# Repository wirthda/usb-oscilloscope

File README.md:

# Introduction
This repository serves as documentation and overview of the project **USB-oscilloscope**,
which was carried out in the summer semester 2025 at the efi faculty of the University of Applied Sciences Nuremberg (Georg-Simon-Ohm).
# Overview
### Project structure:

<ins>legend:</ins>\
HW - hardware\
FW - firmware\
SW - software

### USB oscilloscope prototype:

### Documentation:
PDF [GER]: [Dokumentation_Projekt_USB_Oszi.pdf](docs/documentation/LATEX_german/Dokumentation_Projekt_USB_Oszi.pdf)

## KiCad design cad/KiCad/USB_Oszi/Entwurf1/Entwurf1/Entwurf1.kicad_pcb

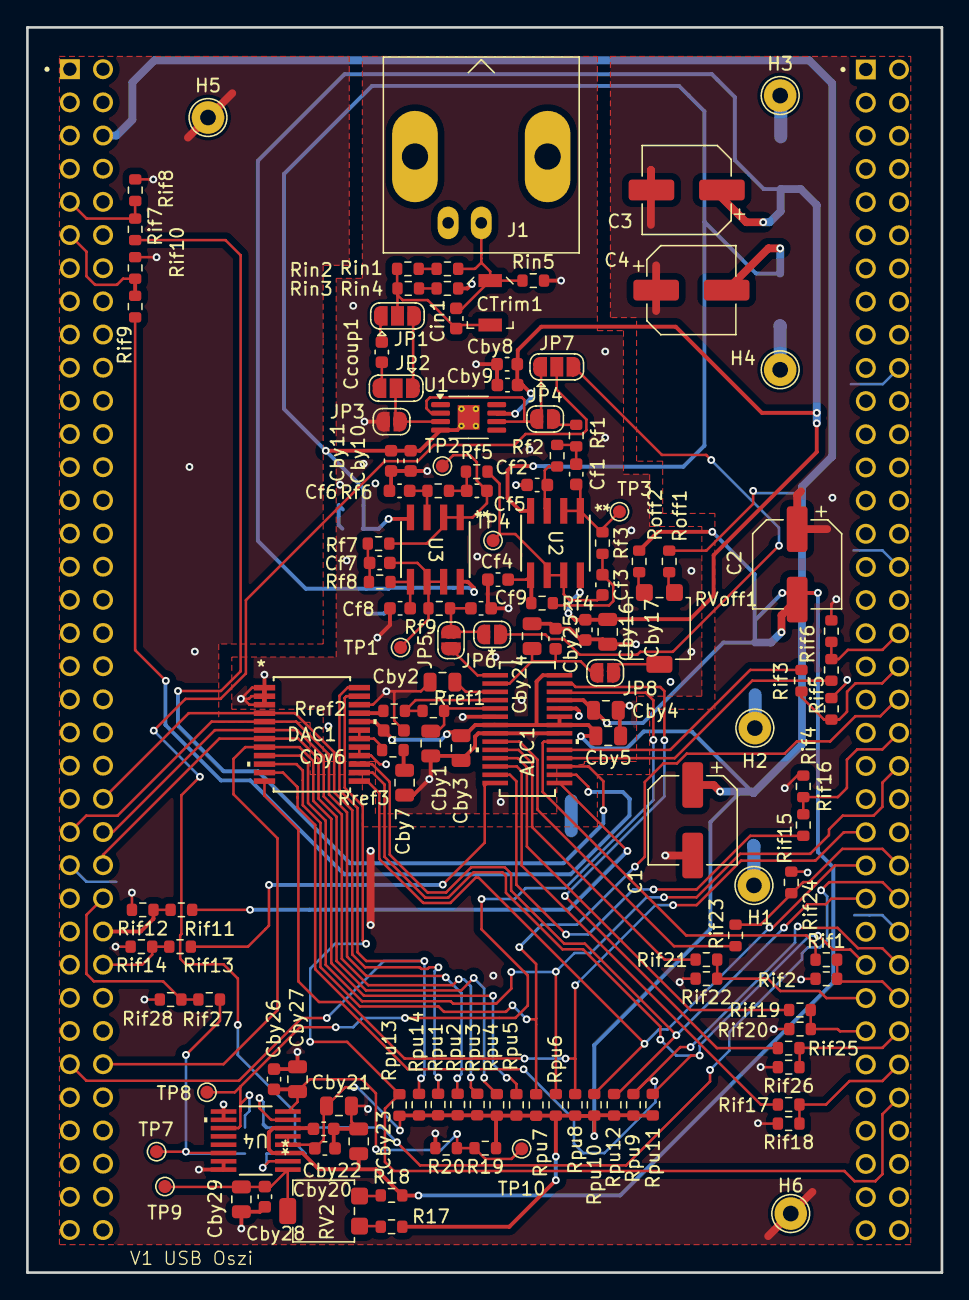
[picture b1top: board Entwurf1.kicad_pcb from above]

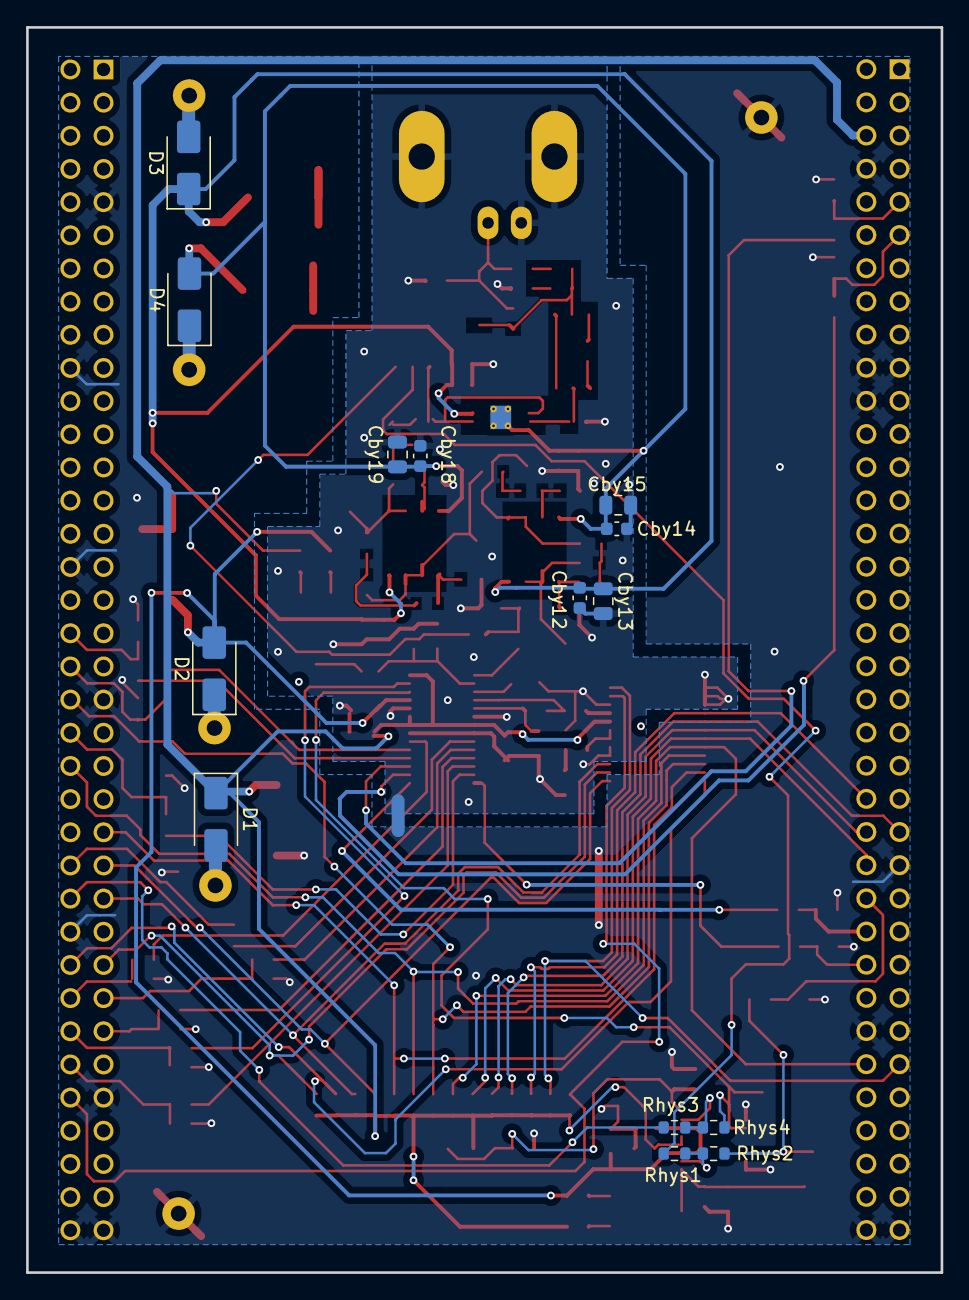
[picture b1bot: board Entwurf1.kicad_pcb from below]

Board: 2 copper layers, 70.0 x 95.4 mm, 150 parts (14 on the bottom side), 95 nets.

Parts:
A1: NUCLEO-F767ZI; ST_NUCLEO-F767ZI
ADC1: LTC1420CGN-PBF; FOOTPRINT_ADC_USB_OSZI
C1, C2, C3, C4: C_Polarized; CP_Elec_6.3x7.7
CTrim1: Cin2; C_Trimmer_Voltronics_JR
Cby1, Cby2, Cby3, Cby4, Cby5, Cby24: 1u; C_0805_2012Metric
Cby6, Cby8, Cby10, Cby12, Cby14, Cby16, Cby18, Cby20, Cby22, Cby26, Cby28: 0.1u; C_0603_1608Metric
Cby7, Cby21, Cby23, Cby27, Cby29: 4.7u; C_0805_2012Metric
Cby9, Cby11: 100p; C_0603_1608Metric
Cby13, Cby15, Cby17, Cby19: 10u; C_0805_2012Metric
Cby25: 100n; C_0603_1608Metric
Ccoup1: C; C_0603_1608Metric
Cf1, Cf2, Cf3, Cf4, Cf5, Cf6, Cf7, Cf8, Cf9: C; C_0603_1608Metric
Cin1: C; C_0603_1608Metric
D1, D2, D3, D4: D_Schottky; D_SMA
DAC1: LTC1450CG-PBF; SSOP-24_G_LIT
H1: +5V; TestPoint_THTPad_D2.5mm_Drill1.2mm
H2: -5V; TestPoint_THTPad_D2.5mm_Drill1.2mm
H3: V+; TestPoint_THTPad_D2.5mm_Drill1.2mm
H4: V-; TestPoint_THTPad_D2.5mm_Drill1.2mm
H5, H6: GND; TestPoint_THTPad_D2.5mm_Drill1.2mm
J1: BNC_CH1; BNC_Amphenol_B6252HB-NPP3G-50_Horizontal
JP1, JP2, JP7: coupling; SolderJumper-3_P1.3mm_Open_RoundedPad1.0x1.5mm
JP3, JP4, JP5, JP6, JP8: coupling; SolderJumper-2_P1.3mm_Open_RoundedPad1.0x1.5mm
R17, R18: 820; R_0603_1608Metric
R19: 68k; R_0603_1608Metric
R20: 33k; R_0603_1608Metric
RV2: 10k; Potentiometer_Bourns_3314G_Vertical
RVoff1: 5k; Potentiometer_Bourns_3314G_Vertical
Rf1, Rf2, Rf3, Rf4, Rf5, Rf6, Rf7, Rf8, Rf9: R; R_0603_1608Metric
Rhys1, Rhys3: 100; R_0603_1608Metric
Rhys2, Rhys4: 50k; R_0603_1608Metric
Rif1, Rif2, Rif3, Rif4, Rif5, Rif6, Rif7, Rif8, Rif9, Rif10, Rif11, Rif12, Rif13, Rif14, Rif15, Rif16, Rif17, Rif18, Rif19, Rif20, Rif21, Rif22, Rif23, Rif24, Rif25, Rif26, Rif27, Rif28: R; R_0603_1608Metric
Rin1: 30k; R_0603_1608Metric
Rin2: 560k; R_0603_1608Metric
Rin3: 20k; R_0603_1608Metric
Rin4: 390k; R_0603_1608Metric
Rin5: 50; R_0603_1608Metric
Roff1, Roff2: 2.7k; R_0603_1608Metric
Rpu1, Rpu2, Rpu3, Rpu4, Rpu5, Rpu6, Rpu7, Rpu8, Rpu9, Rpu10, Rpu11, Rpu12, Rpu13, Rpu14: 10k; R_0603_1608Metric
Rref1, Rref2: 5k; R_0603_1608Metric
Rref3: 10; R_0603_1608Metric
TP1: OPV4_OUT; TestPoint_Pad_D1.0mm
TP2: OPV3_OUT; TestPoint_Pad_D1.0mm
TP3: OPV1_OUT; TestPoint_Pad_D1.0mm
TP4: OPV2_OUT; TestPoint_Pad_D1.0mm
TP7: TRIGGER; TestPoint_Pad_D1.0mm
TP8: 5V_CLK; TestPoint_Pad_D1.0mm
TP9: TRIGGER_REF; TestPoint_Pad_D1.0mm
TP10: CLK_REF; TestPoint_Pad_D1.0mm
U1: THS4631DGN; MSOP-8-1EP_3x3mm_P0.65mm_EP1.68x1.88mm_ThermalVias
U2, U3: AD8022ARZ-REEL7; R_8_ADI
U4: LT1714CGN-PBF; SSOP-16_GN_LIT

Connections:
+5V: A1.CN11_6 (E5V), ADC1.7 (VDD), ADC1.22 (OVDD), ADC1.23 (VDD), ADC1.28 (GAIN), C1.1, Cby3.1, Cby5.2, Cby6.1, Cby20.1, Cby21.1, D1.1 (K), DAC1.20 (VCC), R17.1, R19.1, Roff1.1, Rpu1.1, Rpu2.1, Rpu3.1, Rpu4.1, Rpu5.1, Rpu6.1, Rpu7.1, Rpu8.1, Rpu9.1, Rpu10.1, Rpu11.1, Rpu12.1, Rpu13.1, Rpu14.1, U4.4 (V+), U4.5 (V+)
-5V: ADC1.25 (VSS), C2.2, Cby4.1, Cby22.1, Cby23.1, D2.2 (A), R18.2, Roff2.2, U4.3 (V-), U4.6 (V-)
/ADC1/ADC1_CLK: ADC1.26 (CLK), Rhys4.2, TP8.1, U4.11 (QB)
/ADC1/ADC1_D0: ADC1.20 (D0), Rif1.1
/ADC1/ADC1_D1: ADC1.19 (D1), Rif3.1
/ADC1/ADC1_D2: ADC1.18 (D2), Rif5.1
/ADC1/ADC1_D3: ADC1.17 (D3), Rif7.1
/ADC1/ADC1_D4: ADC1.16 (D4), Rif9.1
/ADC1/ADC1_D5: ADC1.15 (D5), Rif11.1
/ADC1/ADC1_D6: ADC1.14 (D6), Rif13.1
/ADC1/ADC1_D7: ADC1.13 (D7), Rif15.1
/ADC1/ADC1_D8: ADC1.12 (D8), Rif17.1
/ADC1/ADC1_D9: ADC1.11 (D9), Rif19.1
/ADC1/ADC1_D10: ADC1.10 (D10), Rif21.1
/ADC1/ADC1_D11: ADC1.9 (D11(MSB)), Rif23.1
/ADC1/ADC1_INPUT: ADC1.1 (+AIN), JP5.2 (B)
/ADC1/ADC1_OF_BIT: ADC1.27 (OF), Rif25.1
/ADC1/DAC1_CLEAR_LOW_ACTIVE: A1.CN12_64 (PE0), DAC1.23 (*CLR), Rpu13.2
/ADC1/DAC1_LOAD_LOW_ACTIVE: A1.CN11_61 (PE1), DAC1.24 (*LDAC), Rpu14.2
/Analog Frontend CH1/ANALOG_INPUT: CTrim1.1, Cin1.1, J1.1 (In), Rin1.1, Rin5.1
/Analog Frontend CH1/TRIGGER_SIGNAL: JP7.2 (C), Rhys1.1
/Connector uC/PE2: A1.CN11_46 (PE2), DAC1.4 ((LSB)D0), Rpu1.2
/Connector uC/PE3: A1.CN11_47 (PE3), DAC1.5 (D1), Rpu2.2
/Connector uC/PE4: A1.CN11_48 (PE4), DAC1.6 (D2), Rpu3.2
/Connector uC/PE5: A1.CN11_50 (PE5), DAC1.7 (D3), Rpu4.2
/Connector uC/PE6: A1.CN11_62 (PE6), DAC1.8 (D4), Rpu5.2
/Connector uC/PE7: A1.CN12_44 (PE7), DAC1.9 (D5), Rpu6.2
/Connector uC/PE8: A1.CN12_40 (PE8), DAC1.10 (D6), Rpu7.2
/Connector uC/PE9: A1.CN12_52 (PE9), Rhys3.1
/Connector uC/PE10: A1.CN12_47 (PE10), DAC1.11 (D7), Rpu8.2
/Connector uC/PE11: A1.CN12_56 (PE11), DAC1.12 (D8), Rpu9.2
/Connector uC/PE12: A1.CN12_49 (PE12), DAC1.13 (D9), Rpu10.2
/Connector uC/PE13: A1.CN12_55 (PE13), DAC1.14 (D10), Rpu11.2
/Connector uC/PE14: A1.CN12_51 (PE14), DAC1.15 (D11(MSB)), Rpu12.2
/Connector uC/PF2: A1.CN11_52 (PF2), Rif27.2, Rif28.1
/Connector uC/PF3: A1.CN12_58 (PF3), Rif1.2, Rif2.1
/Connector uC/PF4: A1.CN12_38 (PF4), Rif3.2, Rif4.1
/Connector uC/PF5: A1.CN12_36 (PF5), Rif5.2, Rif6.1
/Connector uC/PF6: A1.CN11_9 (PF6), Rif7.2, Rif8.1
/Connector uC/PF7: A1.CN11_11 (PF7), Rif9.2, Rif10.1
/Connector uC/PF8: A1.CN11_54 (PF8), Rif11.2, Rif12.1
/Connector uC/PF9: A1.CN11_56 (PF9), Rif13.2, Rif14.1
/Connector uC/PF10: A1.CN12_42 (PF10), Rif15.2, Rif16.1
/Connector uC/PF11: A1.CN12_62 (PF11), Rif17.2, Rif18.1
/Connector uC/PF12: A1.CN12_59 (PF12), Rif19.2, Rif20.1
/Connector uC/PF13: A1.CN12_57 (PF13), Rif21.2, Rif22.1
/Connector uC/PF14: A1.CN12_50 (PF14), Rif23.2, Rif24.1
/Connector uC/PF15: A1.CN12_60 (PF15), Rif25.2, Rif26.1
/Interface uC/5V_TRIGGERED_SIG_IN: Rhys2.1, Rif27.1, TP7.1, U4.14 (QA)
GNDA: A1.CN11_8 (GND_CN11), A1.CN11_19 (GND_CN11__1), A1.CN11_20 (GND_CN11__2), A1.CN11_22 (GND_CN11__3), A1.CN11_49 (GND_CN11__4), A1.CN11_60 (GND_CN11__5), A1.CN11_71 (GND_CN11__6), A1.CN11_72 (GND_CN11__7), A1.CN12_9 (GND_CN12), A1.CN12_20 (GND_CN12__1), A1.CN12_32 (AGND_CN12), A1.CN12_39 (GND_CN12__2), A1.CN12_54 (GND_CN12__3), A1.CN12_63 (GND_CN12__4), A1.CN12_71 (GND_CN12__5), A1.CN12_72 (GND_CN12__6), ADC1.6 (GND), ADC1.8 (GND), ADC1.21 (OGND), ADC1.24 (GND), C1.2, C2.1, C3.2, C4.1, Cby1.2, Cby2.2, Cby3.2, Cby4.2, Cby5.1, Cby6.2, Cby7.2, Cby8.2, Cby9.2, Cby10.2, Cby11.2, Cby12.2, Cby13.2, Cby14.2, Cby15.2, Cby16.2, Cby17.2, Cby18.2, Cby19.2, Cby20.2, Cby21.2, Cby22.2, Cby23.2, Cby24.2, Cby25.2, Cby26.2, Cby27.2, Cby28.2, Cby29.2, Cf2.2, Cf4.2, Cf6.2, Cf8.2, Cf9.2, DAC1.1 (*WR), DAC1.2 (*CSLSB), DAC1.3 (*CSMSB), DAC1.16 (GND), DAC1.17 (REFLO), DAC1.22 (X1/X2), H5.1, H6.1, J1.2 (Ext), JP3.2 (B), R20.2, Rif2.2, Rif4.2, Rif6.2, Rif8.2, Rif10.2, Rif12.2, Rif14.2, Rif16.2, Rif18.2, Rif20.2, Rif22.2, Rif24.2, Rif26.2, Rif28.2, Rin4.2, Rin5.2, U4.9 (LATCHENABLEB), U4.10 (GND), U4.15 (GND), U4.16 (LATCHENABLEA)
unnamed: ADC1.2 (-AIN), Cby24.1, Cby25.1, JP8.2 (B)
unnamed: ADC1.4 (SENSE), Rref1.2, Rref2.1
unnamed: ADC1.3 (VCM), Cby2.1
unnamed: ADC1.5 (VREF), Cby1.1, Rref1.1
unnamed: Cby7.1, Rref3.2
unnamed: Cf1.2, Rf1.2, Rf2.1
unnamed: Cf3.1, Rf3.2, Rf4.1
unnamed: Cf5.2, Rf5.2, Rf6.1
unnamed: Cf7.1, Rf7.2, Rf8.1
unnamed: D1.2 (A), H1.1
unnamed: D2.1 (K), H2.1
unnamed: D3.2 (A), H3.1
unnamed: D4.1 (K), H4.1
unnamed: DAC1.18 (REFHI), DAC1.19 (REFOUT), Rref3.1
unnamed: DAC1.21 (VOUT), Rref2.2
unnamed: Ccoup1.1, JP1.1 (A)
unnamed: JP1.3 (B), JP2.1 (A)
unnamed: CTrim1.2, Cin1.2, JP1.2 (C), Rin2.2, Rin3.1
unnamed: Ccoup1.2, JP2.3 (B)
unnamed: JP2.2 (C), JP3.1 (A), U1.3 (+)
unnamed: JP4.1 (A), JP7.1 (A), U1.2 (-), U1.6
unnamed: JP4.2 (B), Rf1.1
unnamed: Cf9.1, JP5.1 (A), JP6.1 (A), Rf9.2
unnamed: JP6.2 (B), JP7.3 (B)
unnamed: JP8.1 (A), RVoff1.2
unnamed: R17.2, RV2.1
unnamed: R18.1, RV2.3
unnamed: RVoff1.1, Roff1.2
unnamed: RVoff1.3, Roff2.1
unnamed: Rin1.2, Rin2.1
unnamed: Rin3.2, Rin4.1
unnamed: Cf2.1, Rf2.2, U2.3 (+IN1)
unnamed: Cf4.1, Rf4.2, U2.5 (+IN2)
unnamed: Cf1.1, Rf3.1, TP3.1, U2.1 (OUT1), U2.2 (-IN1)
unnamed: Cf3.2, Rf5.1, TP4.1, U2.6 (-IN2), U2.7 (OUT2)
unnamed: Cf6.1, Rf6.2, U3.3 (+IN1)
unnamed: Cf8.1, Rf8.2, U3.5 (+IN2)
unnamed: Cf5.1, Rf7.1, TP2.1, U3.1 (OUT1), U3.2 (-IN1)
unnamed: Cf7.2, Rf9.1, TP1.1, U3.6 (-IN2), U3.7 (OUT2)
unnamed: Rhys1.2, Rhys2.2, U4.2 (+INA)
unnamed: Rhys3.2, Rhys4.1, U4.7 (+INB)
unnamed: Cby28.1, Cby29.1, RV2.2, TP9.1, U4.1 (-INA)
unnamed: Cby26.1, Cby27.1, R19.2, R20.1, TP10.1, U4.8 (-INB)
V+: C3.1, Cby8.1, Cby9.1, Cby12.1, Cby13.1, Cby16.1, Cby17.1, D3.1 (K), U1.7 (V+), U2.8 (+VS), U3.8 (+VS)
V-: C4.2, Cby10.1, Cby11.1, Cby14.1, Cby15.1, Cby18.1, Cby19.1, D4.2 (A), U1.4 (V-), U1.9 (PAD), U2.4 (-VS), U3.4 (-VS)

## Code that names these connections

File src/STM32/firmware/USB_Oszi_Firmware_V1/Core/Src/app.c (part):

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 * configures the external DAC (LTC1450) to set the ADC reference voltage in mV
 * according to the variable newReferenceVoltage (value sent over from PC)
 *
 * µC[PE14:PE10, PE8:PE2] --> DAC[D11:D0]
 * PE0: /CLEAR
 * PE1: /LOAD
 * 														*/
void configureReferenceVoltage()
{
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
	uint16_t DAC_ODR_val = 0, temp;

	// set bits DAC[D0:D6] ( µC[PE2:PE8] )
	temp = DAC_val & MASK_D0_D6;				// extract DAC[D0:D6]
	DAC_ODR_val |= (temp << 2);		// prepare assignment to µC[PE2:PE8]
	// set bits DAC[D7:D11] ( µC[PE10:PE14] )
	temp = (DAC_val & MASK_D7_D11) >> 7;			// extract DAC[D7:D11] and flush right
	DAC_ODR_val |= (temp << 10);		// prepare assignment to µC[PE10:PE14]

	// clear µC[PE2:PE8, PE10:PE14]
	GPIOE->ODR &= ~(GPIO_ODR_OD2|GPIO_ODR_OD3|GPIO_ODR_OD4|GPIO_ODR_OD5|GPIO_ODR_OD6|GPIO_ODR_OD7|GPIO_ODR_OD8|
				    GPIO_ODR_OD10|GPIO_ODR_OD11|GPIO_ODR_OD12|GPIO_ODR_OD13|GPIO_ODR_OD14);
	GPIOE->ODR |= DAC_ODR_val;					// assign DAC[D0:D11]
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	/* --- ADC-GPIOs --- */

	/* GPIOs for ADC parallel interface
	 * ADC[D11:D0] --> µC[PF14:PF3]	*/
	/* enable clock for GPIOF */
	RCC->AHB1ENR |= RCC_AHB1ENR_GPIOFEN;
	// PF3...14->input (MODE: 0b00)
	GPIOF->MODER &= ~(GPIO_MODER_MODER3_Msk|GPIO_MODER_MODER4_Msk|GPIO_MODER_MODER5_Msk|GPIO_MODER_MODER6_Msk|
					  GPIO_MODER_MODER7_Msk|GPIO_MODER_MODER8_Msk|GPIO_MODER_MODER9_Msk|GPIO_MODER_MODER10_Msk|
					  GPIO_MODER_MODER11_Msk|GPIO_MODER_MODER12_Msk|GPIO_MODER_MODER13_Msk|GPIO_MODER_MODER14_Msk);
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	GPIOF->PUPDR |= GPIO_PUPDR_PUPDR15_1|GPIO_PUPDR_PUPDR2_1|GPIO_PUPDR_PUPDR1_1|GPIO_PUPDR_PUPDR0_1;

	/* GPIO for ADC Overflow Flag
	 * ADC[OF_BIT] --> µC[PF15]	 	*/
	/* enable clock for GPIOF */
	RCC->AHB1ENR |= RCC_AHB1ENR_GPIOFEN;
	// PF15->input (MODE: 0b00)
	GPIOF->MODER &= ~(GPIO_MODER_MODER15_Msk);

	/* GPIO for Trigger
	 * TRIGGERED_SIG_OUT --> µC[PF2]*/
	/* enable clock for GPIOF */
	RCC->AHB1ENR |= RCC_AHB1ENR_GPIOFEN;
	// PF2->input (MODE: 0b00)
	GPIOF->MODER &= ~(GPIO_MODER_MODER2_Msk);


	/* GPIO for TIMer output compare event
	 * PE9: TIM1_CH1 (AF1)
	 * clock for ADC, triggers DMA2 channel 6 stream 5 transfers*/
	/* enable clock for GPIOE */
	RCC->AHB1ENR |= RCC_AHB1ENR_GPIOEEN;
	// PE9->alternate function (MODE: 0b10)
	GPIOE->MODER &= ~GPIO_MODER_MODER9_Msk;
	GPIOE->MODER |= GPIO_MODER_MODER9_1;
	// output speed (very high speed: 0b11)
	GPIOE->OSPEEDR |= (GPIO_OSPEEDR_OSPEEDR9_1|GPIO_OSPEEDR_OSPEEDR9_0);
	// select alternate function AF1 of PE9 (TIM1_CH1)
	GPIOE->AFR[1] &= ~(GPIO_AFRH_AFRH1);
	GPIOE->AFR[1] |= GPIO_AFRH_AFRH1_0;

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	/* --- DAC-GPIOs --- */

	/* GPIOs for DAC parallel interface
	 * µC[PE14:PE10, PE8:PE2] --> DAC[D11:D0]	*/
	/* enable clock for GPIOE */
	RCC->AHB1ENR |= RCC_AHB1ENR_GPIOEEN;
	// PE2...8 & PE10...14->output (MODE: 0b01)
	GPIOE->MODER &= ~(GPIO_MODER_MODER2_Msk|GPIO_MODER_MODER3_Msk|GPIO_MODER_MODER4_Msk|GPIO_MODER_MODER5_Msk|
					  GPIO_MODER_MODER6_Msk|GPIO_MODER_MODER7_Msk|GPIO_MODER_MODER8_Msk|GPIO_MODER_MODER10_Msk|
					  GPIO_MODER_MODER11_Msk|GPIO_MODER_MODER12_Msk|GPIO_MODER_MODER13_Msk|GPIO_MODER_MODER14_Msk);
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					  GPIO_OTYPER_OT8|GPIO_OTYPER_OT10|GPIO_OTYPER_OT11|GPIO_OTYPER_OT12|GPIO_OTYPER_OT13|GPIO_OTYPER_OT14);

	/* GPIOs for DAC CLEAR and LOAD
	 * PE0: /CLEAR
	 * PE1: /LOAD 		*/
	/* enable clock for GPIOE */
	RCC->AHB1ENR |= RCC_AHB1ENR_GPIOEEN;
	// PE0...1->output (MODE: 0b01)
	GPIOE->MODER &= ~(GPIO_MODER_MODER0_Msk|GPIO_MODER_MODER1_Msk);
	GPIOE->MODER |= (GPIO_MODER_MODER0_0|GPIO_MODER_MODER1_0);
	// open-drain outputs (OT=1), external pull-up are used (3V3 -> 5V)
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	NVIC_EnableIRQ(EXTI15_10_IRQn);

	/* EXTI2 Configuration for Trigger Signal */
	// SysCfg configuration EXTI2->PF2
	SYSCFG->EXTICR[0] |= SYSCFG_EXTICR1_EXTI2_PF;
	// mask EXTI13 (deacivated - trigger is activated in sampling state)
	EXTI->IMR &= ~(EXTI_IMR_MR2);
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 *
 * initialization of TIM1
 * TIM1 used for triggering DMA transfers
 * and creating a clock signal on PE9 (both are synchronous)
 * transmission is done on falling edge of clock signal (avoid setup-hold-violation)
 *
 *	 													*/
static void TIM1_Init()
{
	/* create ADC-Clock (10MHz) at OC-Pin PE9 (TIM1_CH1)
	 * used timer: TIM1 (APB2)
	 * clock: APB2 Timer Clock: 100MHz */
	// enable TIM1-clock
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
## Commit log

2025-09-24 format measurements and adding the probe setting
2025-09-24 added function set_cursor_diff
2025-09-24 add FW part in documentation (digital filter - recursive)
2025-09-24 FW fix moving average filter and add recursive variant
2025-09-25 Hinzufügen von Grafiken, zur Darstellung der Softwarearchitektur
2025-09-29 add FW part in documentation (implementation)
2025-09-30 changed dach and base measurement
2025-09-30 Software and docu - thx Felix
2025-09-30 Better gitignore
2025-09-30 fixed voltage format
2025-10-01 changed png für multithreading
2025-10-01 add FW part in documentation (fw-test)
2025-10-02 added png for statemachine GUI and SW and added text for Entwurf
2025-10-02 added section Ergebnisse: Benuteroberfläche
2025-10-02 Added Klassendiagramm_GUI
2025-10-02 add figures to firmware test part
2025-10-02 update pdf output of documentation
2025-10-02 add links to python packages (SW)
2025-10-02 doc of main test, results; add figures from test measurements
2025-10-03 added Debug-Window to Ergebnisse and Konzept Benutzeroberfläche to SW
2025-10-03 add SW-FW interface part in doc (usb cdc selection)
2025-10-03 add subsubsection Auswahl und Definition der Messungen in SW Entwurf
2025-10-03 update doc pdf
2025-10-03 added Implementation SW
2025-10-04 add HW part in documentation (hw concept)
2025-10-04 add SW-Test
2025-10-04 doc of main test; add figures from test measurements
2025-10-04 Fixed mistake base measure and added subsection Implementierung GUI und Messfunktionen und Anhang
2025-10-05 add HW part in documentation (hw implementation)
2025-10-05 add HW part in documentation (hw test)
2025-10-05 add HW-FW interface part in documentation
2025-10-05 add HW_FW_interface_Pinbelegung and Test
2025-10-05 add appendix files
2025-10-05 change directory structure
2025-10-06 add abstract, conclusion, outlook in documentation
2025-10-06 doc of HW part (change references to schematic)
2025-10-06 add responsibilities in documentation
2025-10-06 add link to pcb design rules (HW doc)
2025-10-06 correct SW-part
2025-10-06 correct section Zusammenführung and section Ergebnis
2025-10-06 doc fix typos and false references
2025-10-06 update pdf (after merge)
2025-10-06 add titlepage, add reference to hw layout
2025-10-06 change title picture
2025-10-06 add main picture in README
2025-10-07 added text for info-page
